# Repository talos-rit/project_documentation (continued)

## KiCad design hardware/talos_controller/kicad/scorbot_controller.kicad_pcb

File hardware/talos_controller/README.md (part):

# Talos controller board, rev 0.5

A controller board for the Scorbot ER-V and ER-4pc educational arms (the Talos-RIT project's two robots). It replaces the original
controller box with an ESP32-S3-DevKitC-1 on a 265 × 210 mm two-layer board: seven motor channels on plug-in driver
modules (five arm axes, the gripper, the slide rail; the project's own Talos driver module, or the Pololu G2 18v17 the sockets were drawn for), a hardware quadrature counter (LS7366R) and a current sense on every channel,
power from a standard ATX PC supply, a mushroom e-stop with a MOTORS ON relay chain, and ten status pixels. Every part is
through-hole, so the board can be built by hand or partly by a board house.

The firmware ([talos-rit/esp-driver](https://github.com/talos-rit/esp-driver)) speaks the Eshed controller's own serial dialect over the
DevKit's USB socket, so the Raspberry Pi "operator" software and the Pi image are the same for both robots. A protobuf link for the
ROS 2 stack is a second mode on the same socket, picked in the firmware's configuration or detected from the first bytes.

> **Status, 13 November 2026.** The design is rev 0.5: the reviewed rev 0.4 board with one change, two signals moved to other pins
> of the DevKit socket so that the ESP32 boards still on sale fit (section 8). The first order, from JLCPCB with partial
> assembly, is being prepared. No board has been built or powered yet, and the firmware compiles for the ESP32-S3 but has not run on a chip. Read
> everything here as "designed and reviewed, not yet proven"; the open items are listed at the end, and the first-power procedure
> in section 5 exists because the first board is the first test of the design.

Left to right, top to bottom: the seven channel strips (encoder filters, clamps and the LS7366R counters U13 to U19) across the top;
the rail terminal J8, the fan header J7 and its fuse F4 on the top edge; the DevKit socket U1 at the lower left with the I/O
expanders U9, U10 and the ADC boards U11, U12 beside it; the seven driver sockets U2 to U8 in the centre with the motor-rail
capacitors C42 to C45; the 50-pin robot connector J1 on the right edge; the relays K1, K2, the fuses F1, F2 and the ATX headers J2, J3 at
the lower right; the status pixels, the lamps, the MOTORS ON button SW2, the e-stop cut-out and the external e-stop terminal J4 along the
front edge.

## What is in this folder

| File | What it is |
| --- | --- |
| `README.md` | this guide |
| `parts.md` | the parts list by vendor, with quantities and the substitution rules |
| `fab/scorbot_controller_rev0.5_gerbers.zip` and `.sha256` | the manufacturing files (Gerbers and drill files): the zip to order from |
| `fab/jlcpcb_bom.csv`, `fab/jlcpcb_cpl.csv` | the BOM and placement files for JLCPCB's assembly service |
| `fab/hand_assembled.csv` | the parts JLCPCB does not place: what you fit yourself, and why |
| `fab/digikey_upload.csv` | the Digi-Key list, ready for "Upload a list" |
| `purchase_options.md`, `orders/` | three ways of ordering the boards, assembled or bare, with what each costs (carts of 18 November 2026) and the parts list of each cart |
| `schematic.pdf` | the schematic |
| `assembly_map.pdf`, `assembly_map.svg` | every footprint with its reference designator and orientation marks, and a legend of what goes where |
| `images/` | the board's top and bottom views |
| `kicad/` | the KiCad project: board, schematic, the project's symbol and footprint libraries. KiCad 7 format; KiCad 8, 9 and 10 open and upgrade it |

The design document behind the board, with the pin map, the channel design and the firmware's behaviour rules, is
`technical/ros2/esp_controller_design.md` in the project documentation (section 8 describes this board).

## What you need

- Through-hole soldering: about 36 parts to fit yourself (about 200 joints), plus the plug-in modules. A board house does the rest.
- A multimeter, a bench power supply with an adjustable current limit, and a clamp meter for the driver check.
- M3 hardware and standoffs of 15 mm or taller (the e-stop body reaches 12.6 mm below the board); the list is in `parts.md`.
- An ATX PC power supply with a 24-pin main lead and a 4-pin "CPU 12 V" lead.
- A computer with ESP-IDF v5.5.3 to build and flash the firmware, and two micro-USB **data** cables.
- A Raspberry Pi running the operator (the existing Talos-RIT stack), or a PC with the ROS 2 stack.

## 1. Order the board

Upload `fab/scorbot_controller_rev0.5_gerbers.zip` to JLCPCB as it is. Check the sha256 against `fab/scorbot_controller_rev0.5_gerbers.zip.sha256`
first if you copied it around. The options that matter:

| Option | Choose |
| --- | --- |
| Layers, size | 2 layers; 265 × 210 mm is read from the files (type it if the form still shows a default) |
| Material, thickness | FR-4 TG135, 1.6 mm |
| Copper | 1 oz outer copper (the design was checked at 1 oz; 2 oz is also fine with these files) |
| Surface finish | lead-free HASL. Not OSP: the hand-fitted parts are soldered weeks after the boards arrive |
| Colour | any; the white silkscreen on green is the most legible |
| Vias | tented, minimum via 0.3 mm (the design uses 0.4 mm drills) |
| Confirm production file | yes. Expect two remarks: the silkscreen text is 0.8 mm high, under JLCPCB's printed 1.0 mm minimum (accept it; it prints, a little less crisp), and three pads of U21 have an annular ring of exactly 0.20 mm, their minimum |
| Quantity | 5 is the minimum; spares are useful |

**Assembly.** Tick PCB assembly, top side, through-hole. Upload `fab/jlcpcb_bom.csv` as the BOM and `fab/jlcpcb_cpl.csv` as the
placement file. Choose "Economic" (it covers single-side through-hole boards of this size), tooling holes added by JLCPCB, **Confirm
parts placement = Yes** (you get a preview to check every polarised part: the diodes' bands, the electrolytics' stripes, the lamps,
the socket notches, the relays), board cleaning = No (the MOTORS ON switch is not washable), and add this assembly remark:

> All parts are through-hole, top side. Designators JH3-JH20 are 2.54 mm female header strips whose footprints have no pads on purpose:
> each strip is soldered into the holes of the module footprint under it (JH3-JH16 under U2-U8, JH17-JH20 under U11 and U12). Do NOT wash
> or clean the boards after soldering: SW2 (Omron B3F-4055) is not washable.

At the BOM step JLCPCB matches each line to its catalogue by the code in the file; one line, J4, has to be selected by hand (click its Search, enter `C480516`, Select), a quirk of their matcher with that part. A line it cannot match or has no stock for is simply left unticked: that
part moves to your own list (the fallback lines in `parts.md`). Two things to know: the BOM has the same resistor on two lines where it
is fitted flat and upright, which JLCPCB flags as a duplicate (tick both); and a few parts on the BOM are substitutes for the design
part that were accepted on their datasheets, which `fab/jlcpcb_bom.csv` names line by line.

## 2. Order the parts

What a whole order costs, with the boards assembled or bare, is in [`purchase_options.md`](purchase_options.md).

`parts.md` has everything by vendor: Digi-Key (upload `fab/digikey_upload.csv`, then delete the fallback lines you do not need),
the driver modules (five for the arm or seven for all channels: the Talos driver module in [`../talos_driver_module/`](../talos_driver_module/README.md),
designed and reviewed but not yet built or tested, or the Pololu G2 18v17 it replaces, which fits the same sockets), Adafruit and SparkFun (on the Digi-Key list), and
the supply, cables and hardware from anywhere. The rules that must not be broken when substituting are at the end of that file; the
three most important: the DevKit is never a variant ending in **V**, D20 and D25 are silicon rectifiers and never Schottkys, and F2 takes a
**1 A** blade fuse, never the 7.5 A of F1.

## 3. Assemble

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
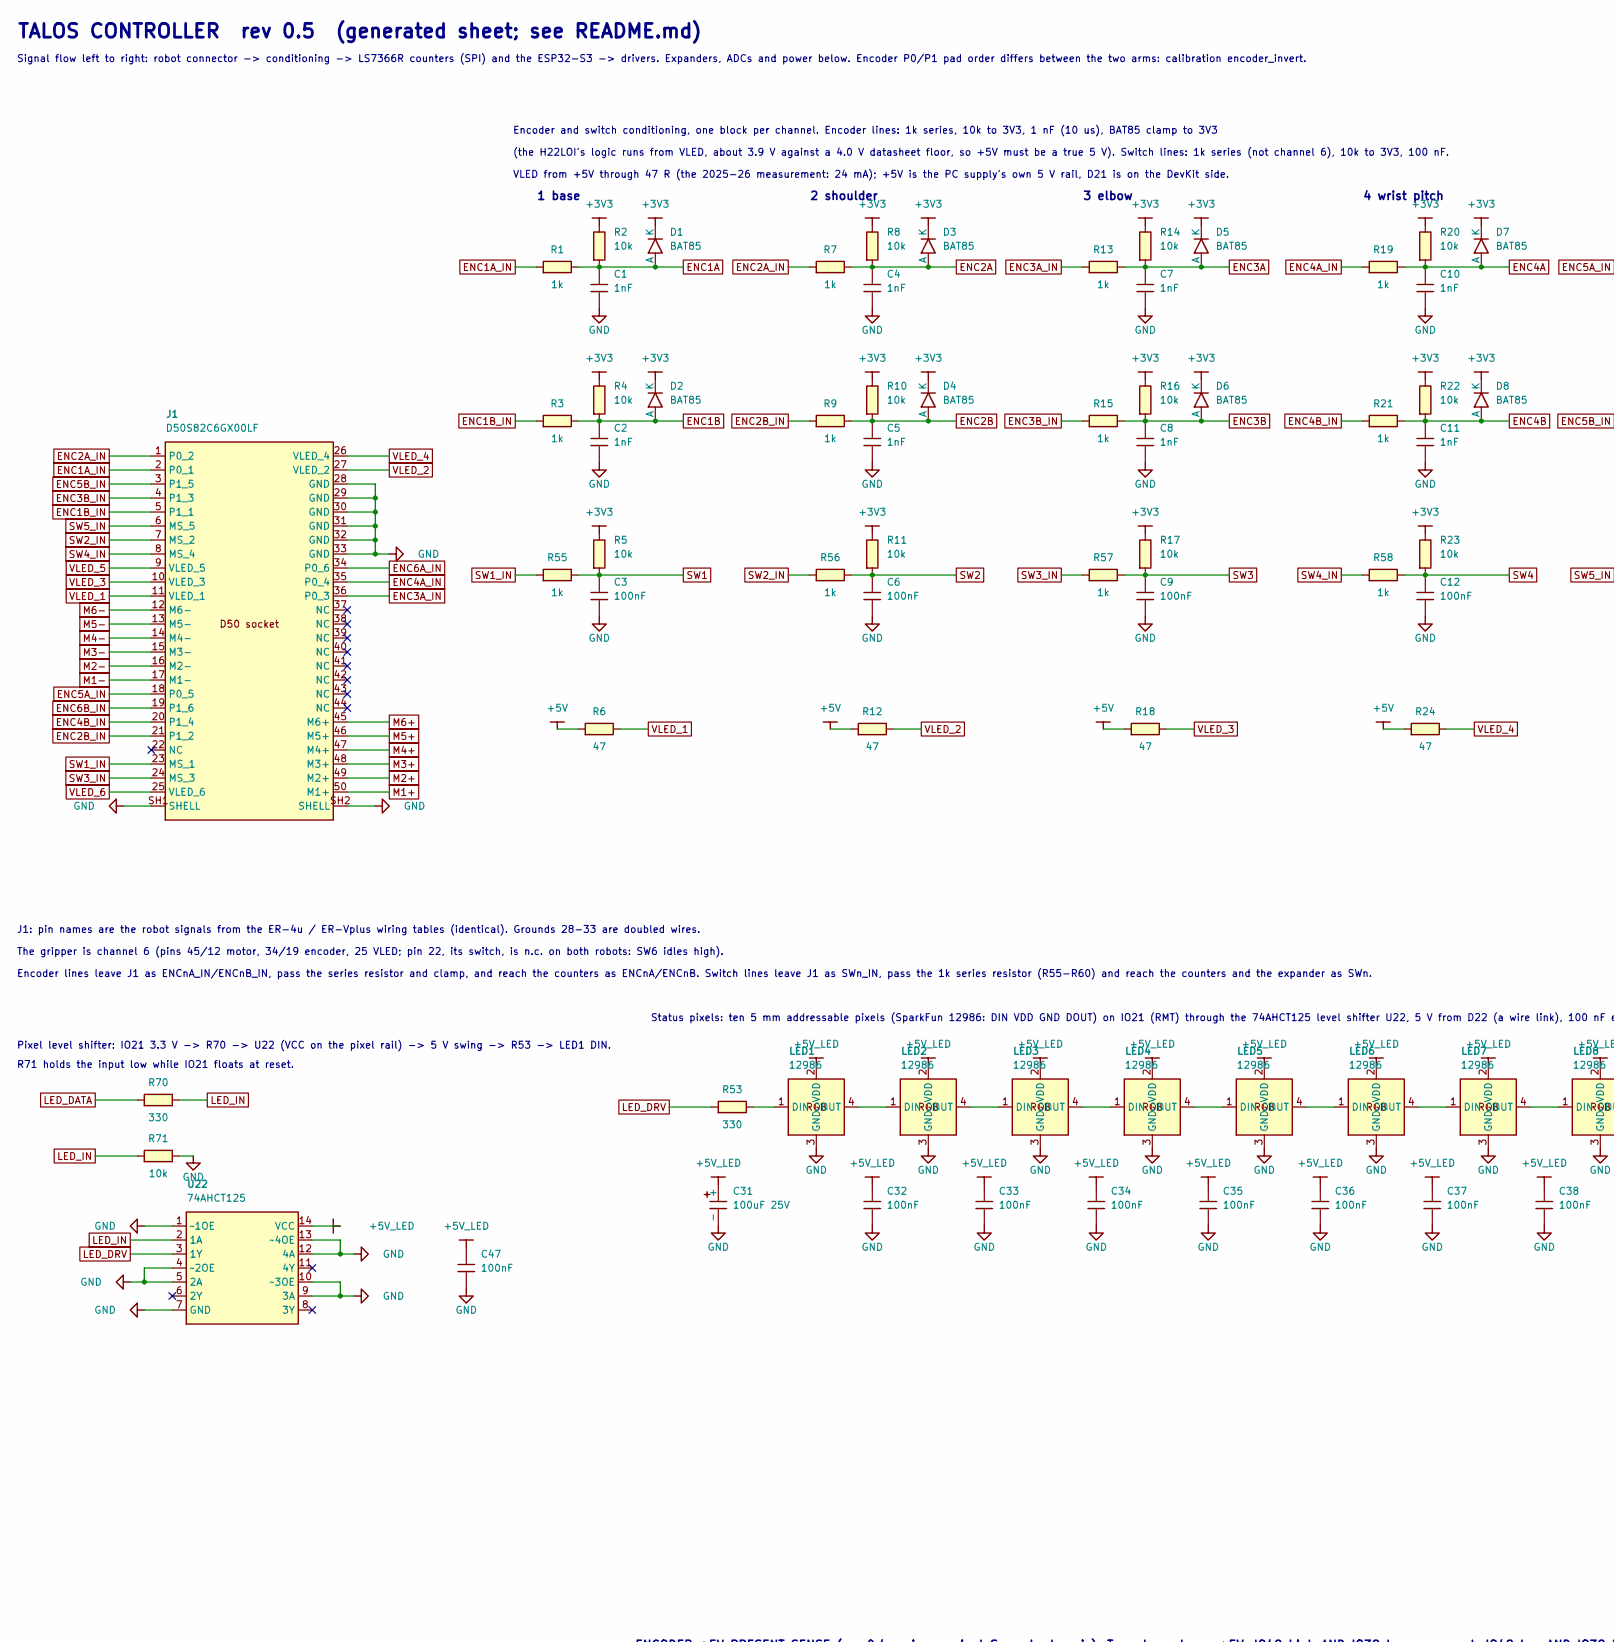
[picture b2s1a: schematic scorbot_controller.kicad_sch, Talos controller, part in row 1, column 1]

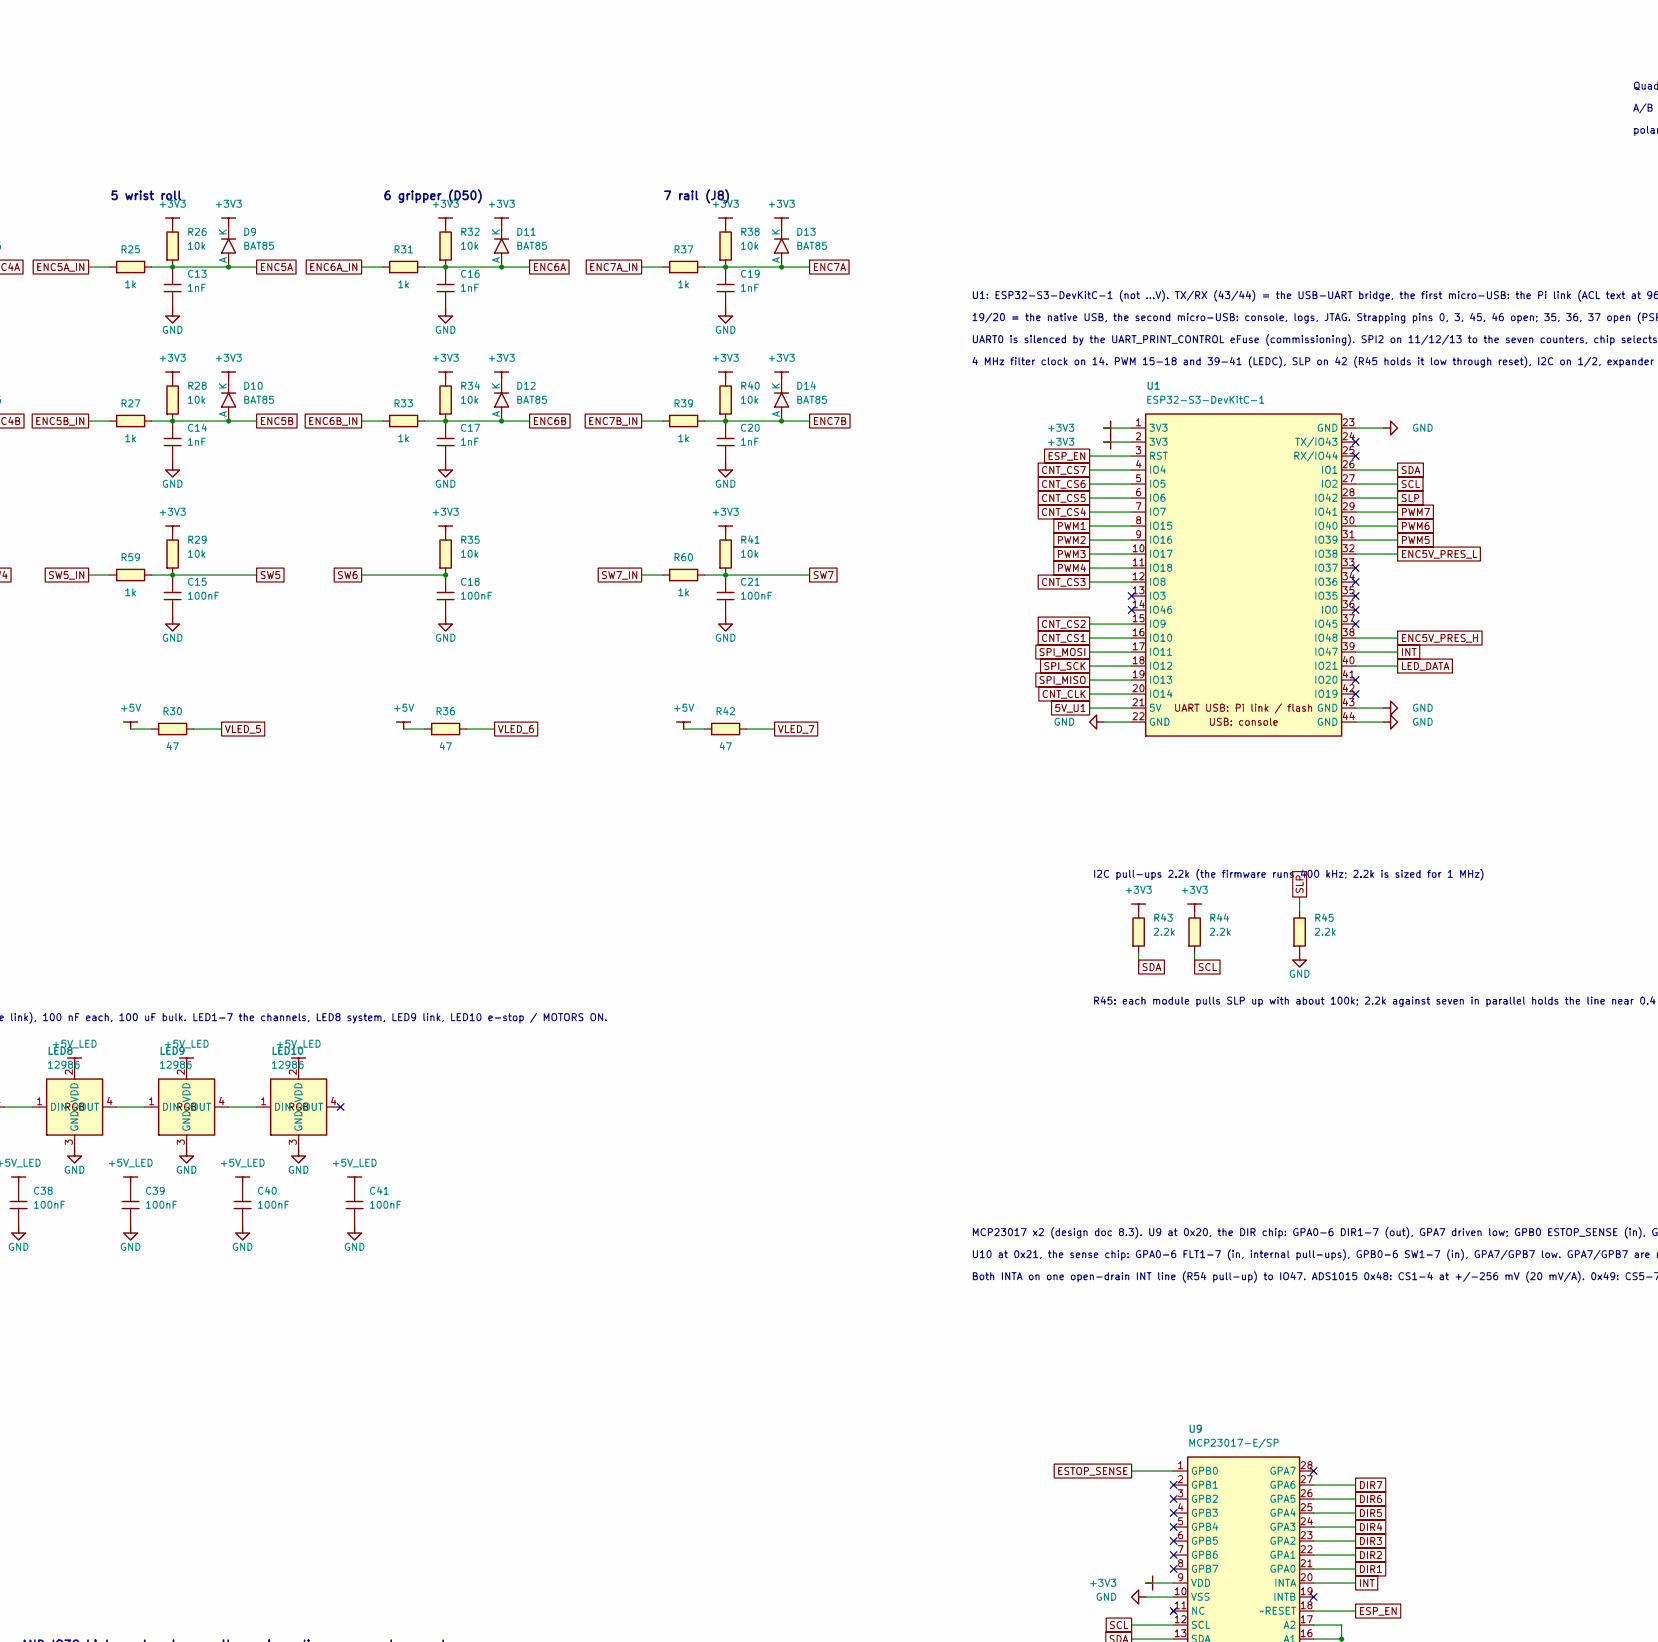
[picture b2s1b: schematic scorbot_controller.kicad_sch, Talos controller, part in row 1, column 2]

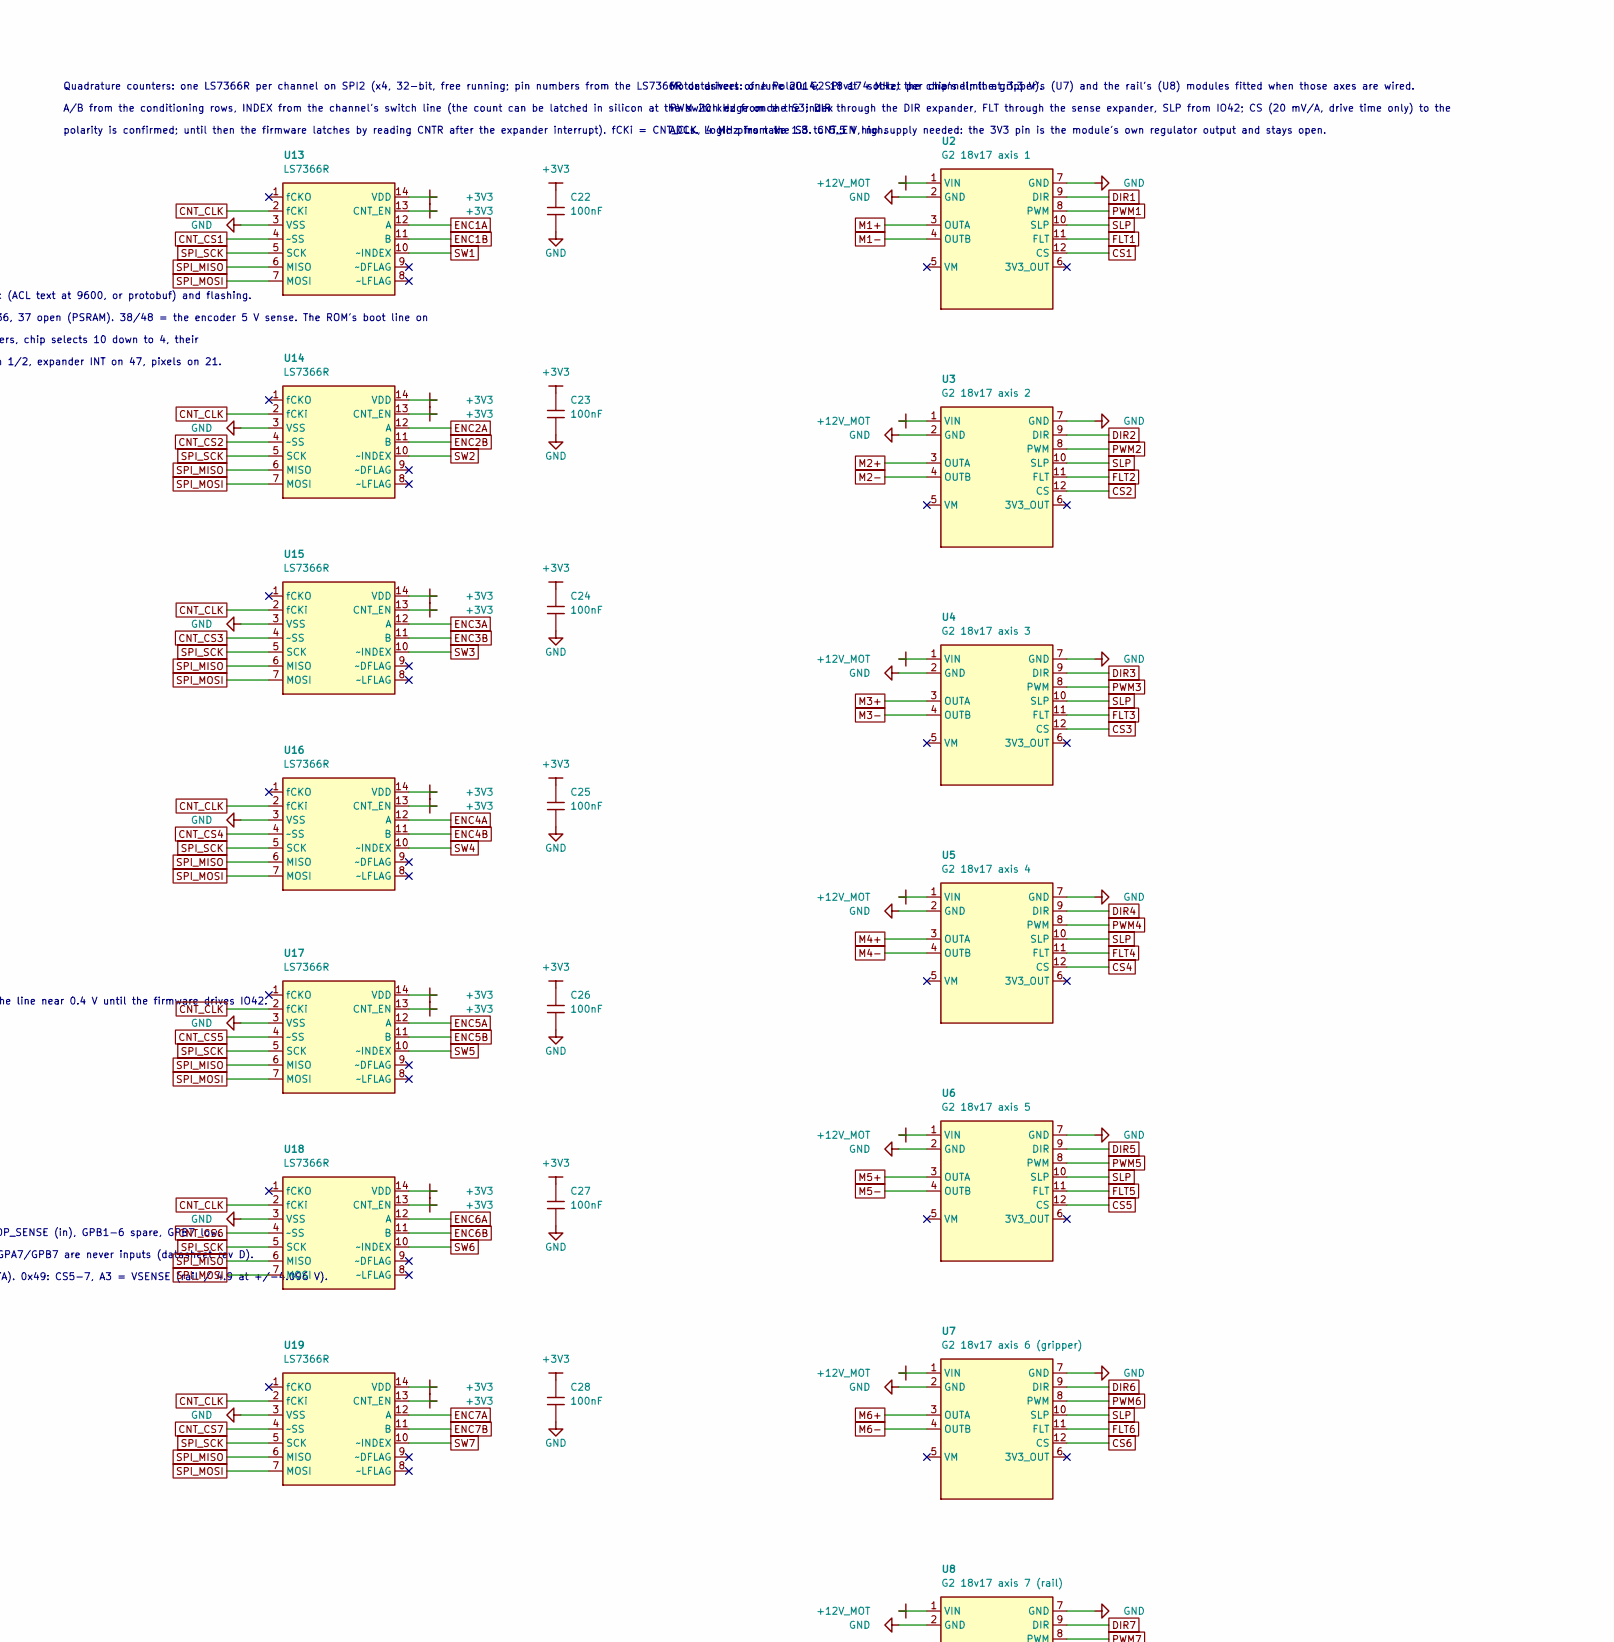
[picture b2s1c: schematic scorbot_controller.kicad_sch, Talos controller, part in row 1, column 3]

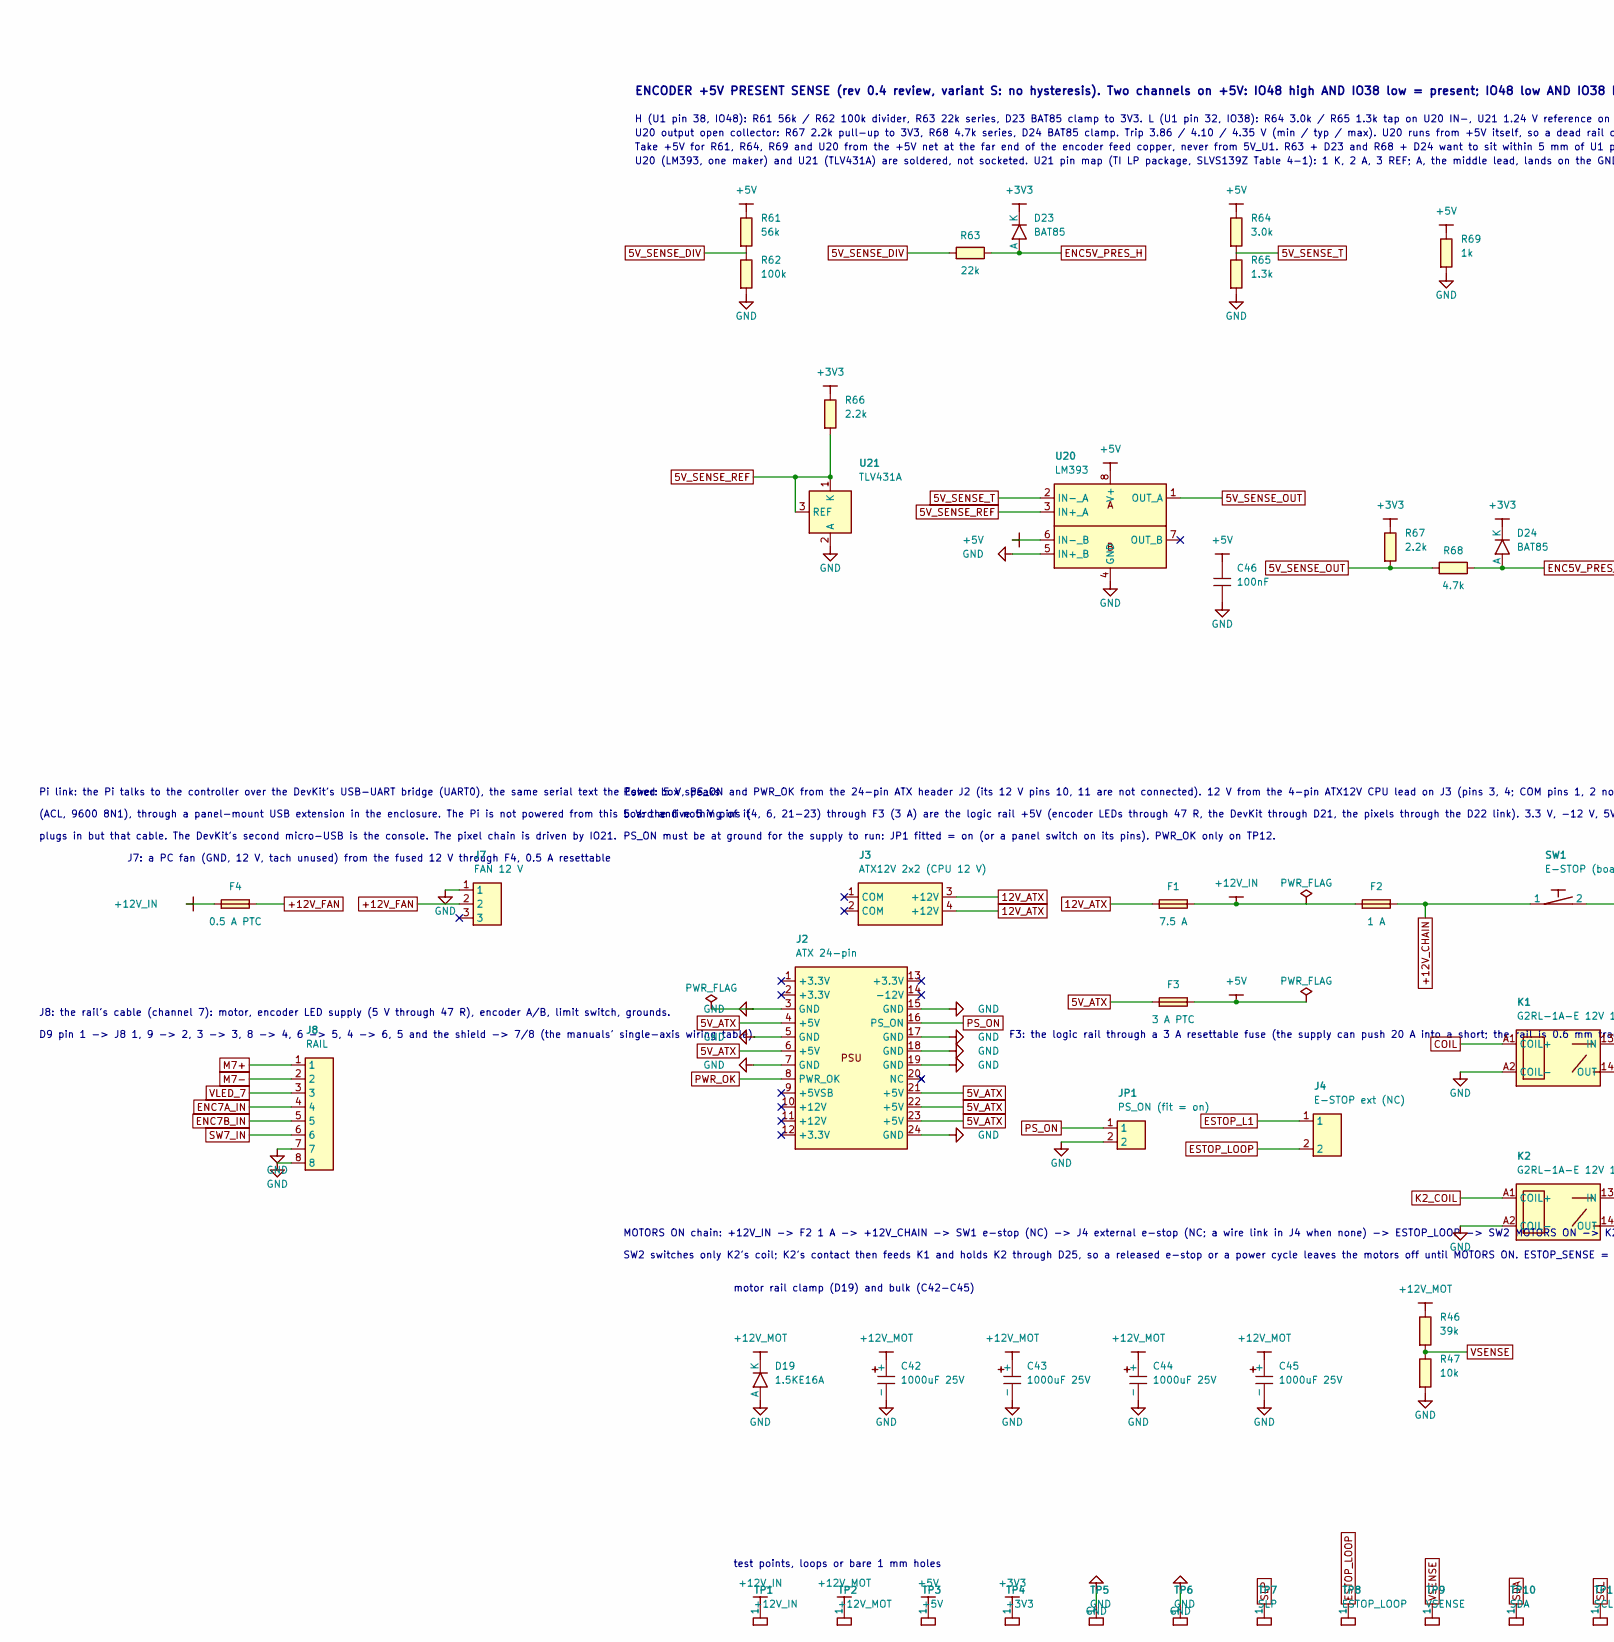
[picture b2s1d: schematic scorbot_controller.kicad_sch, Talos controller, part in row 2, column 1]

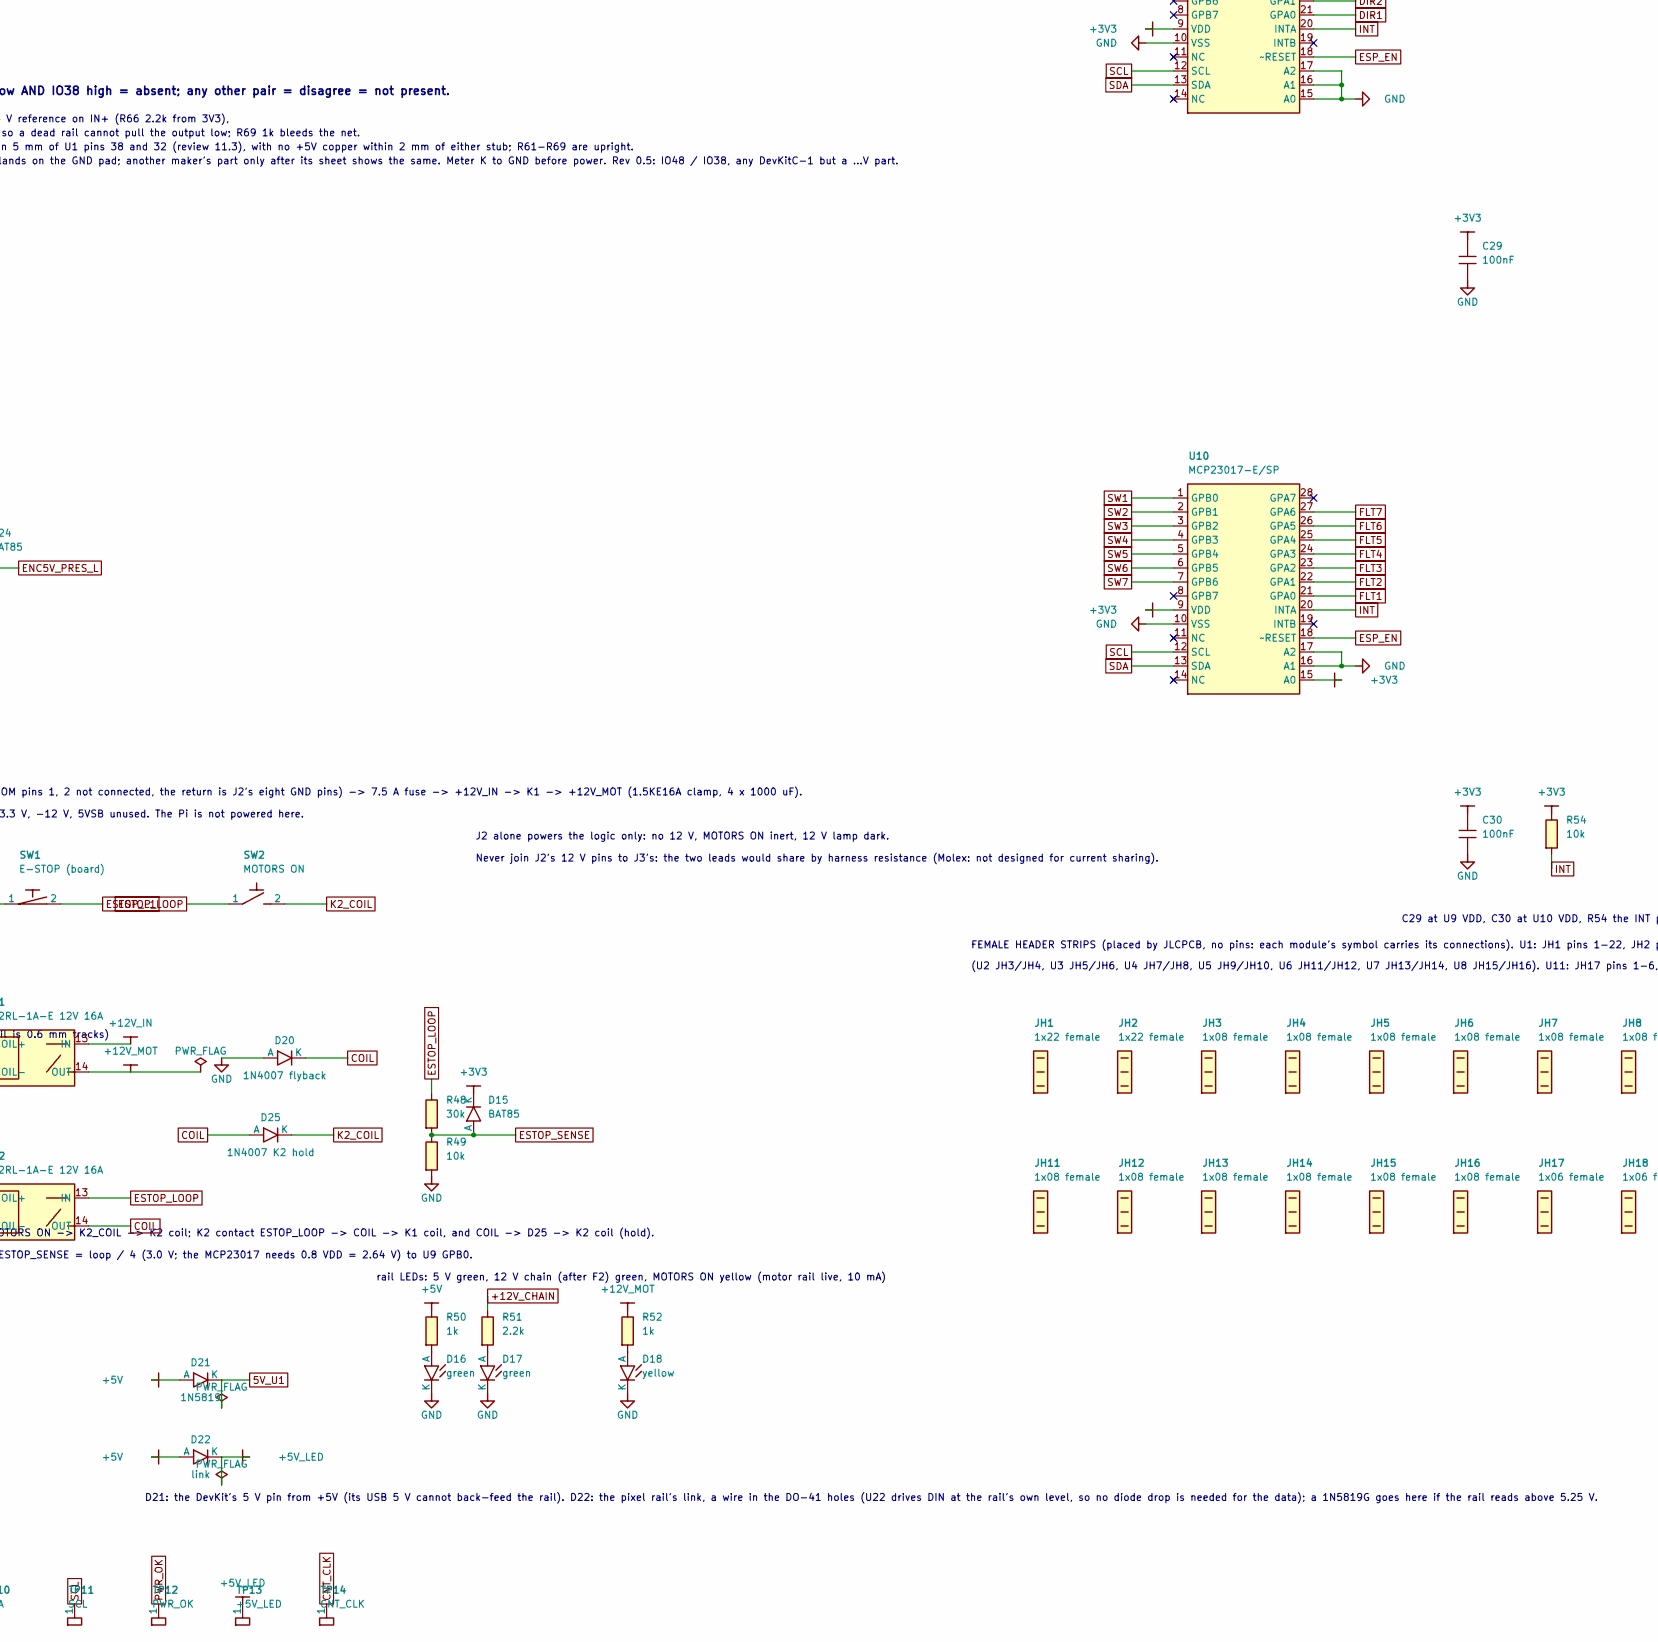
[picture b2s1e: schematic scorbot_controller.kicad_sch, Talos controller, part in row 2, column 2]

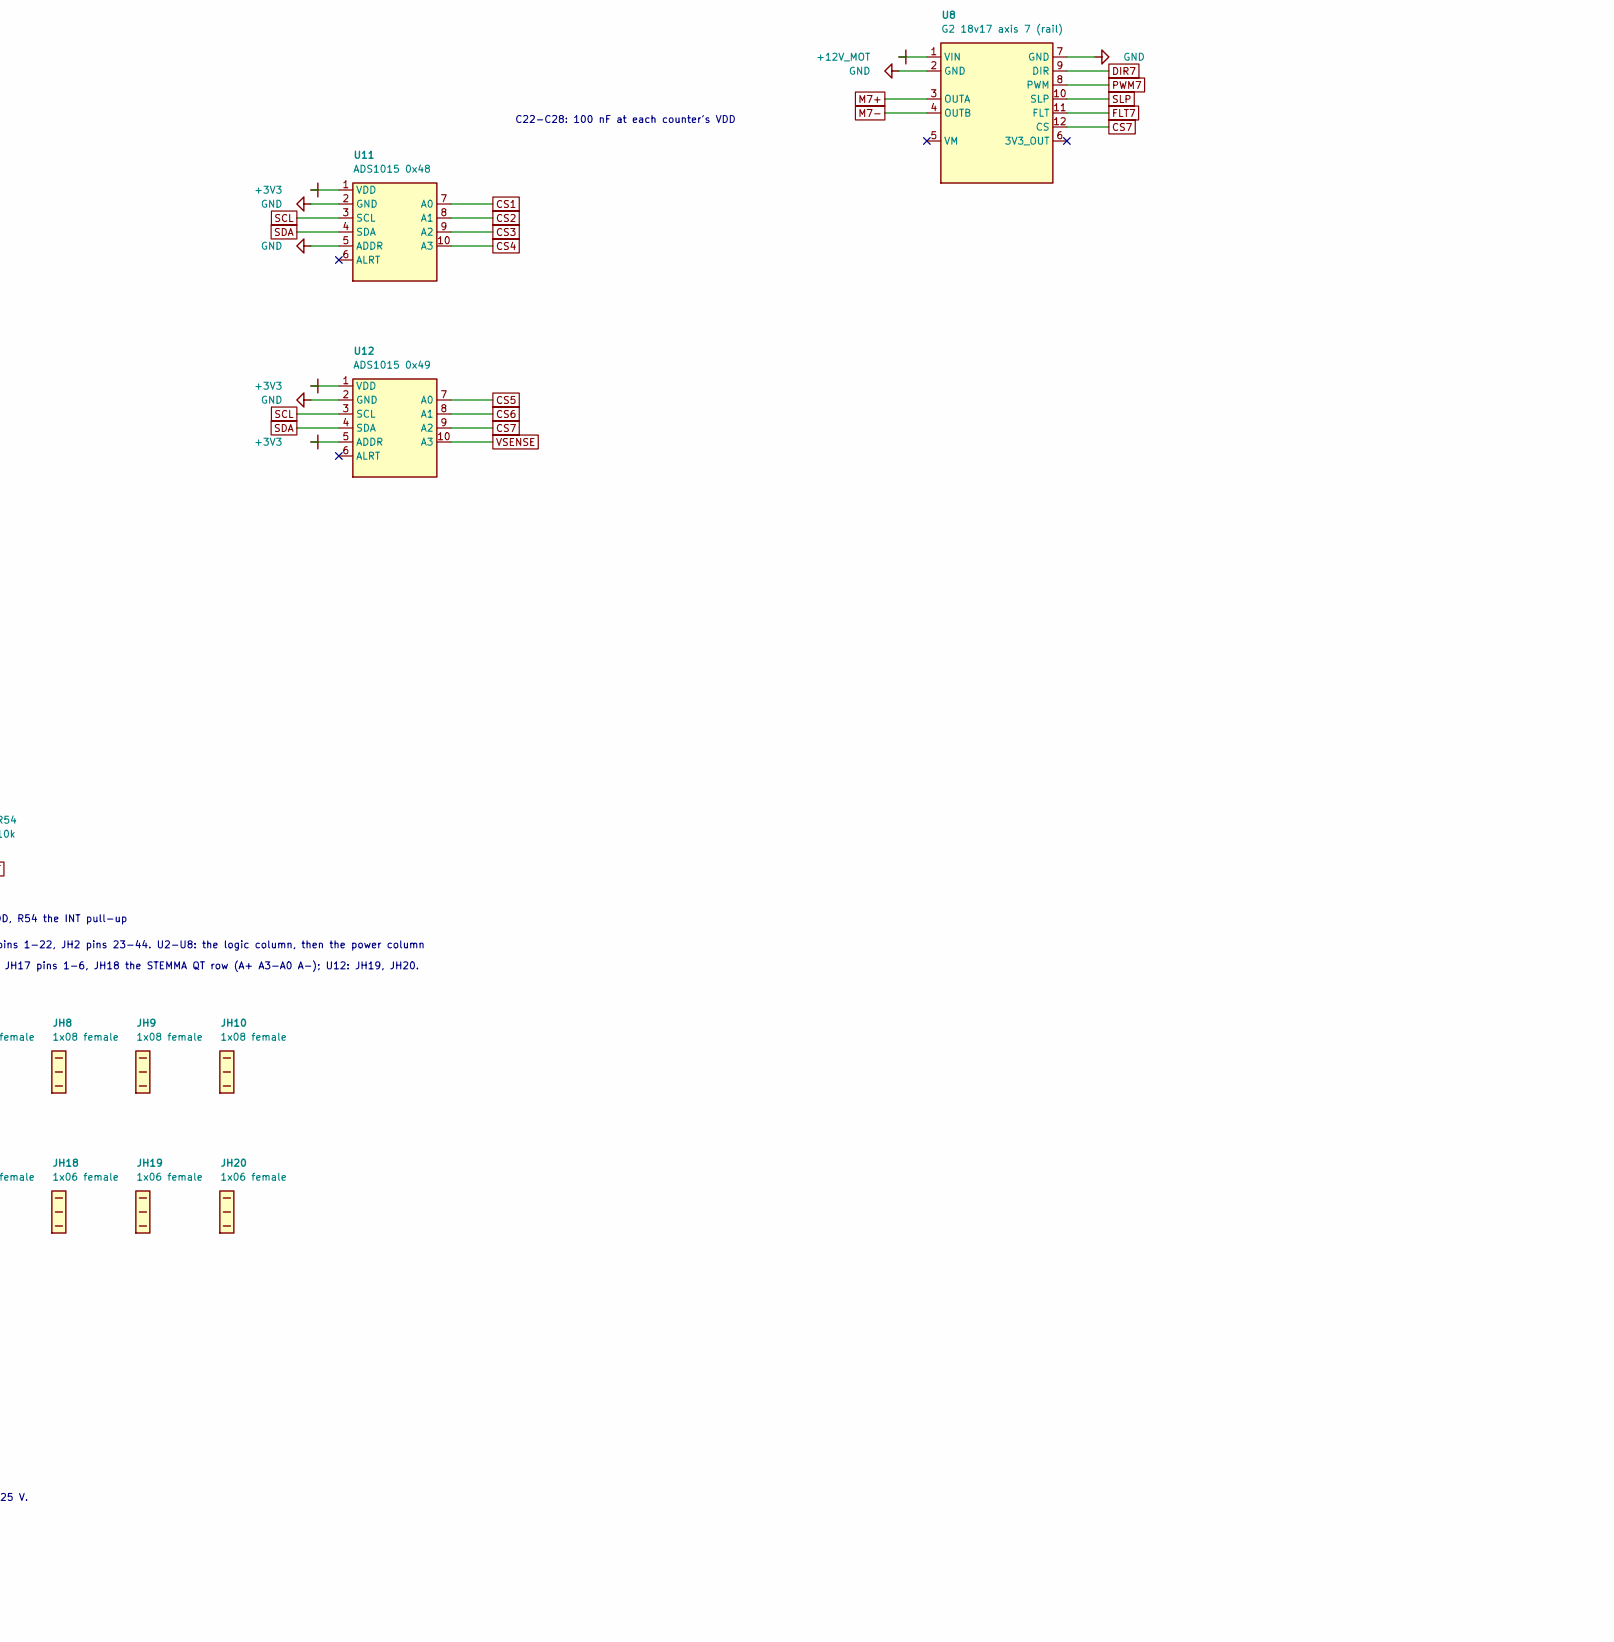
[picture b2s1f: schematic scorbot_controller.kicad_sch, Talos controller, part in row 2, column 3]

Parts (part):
C1, C2, C4, C5, C7, C8, C10, C11, C13, C14, C16, C17, C19, C20: 1nF; C_Disc_D5.0mm_W2.5mm_P5.00mm
C3, C6, C9, C12, C15, C18, C21, C22, C23, C24, C25, C26, C27, C28, C29, C30, C32, C33, C34, C35, C36, C37, C38, C39, C40, C41, C46, C47: 100nF; C_Disc_D5.0mm_W2.5mm_P5.00mm
C31: 100uF 25V; CP_Radial_D6.3mm_P2.50mm
C42, C43, C44, C45: 1000uF 25V; CP_Radial_D10.0mm_P5.00mm
D1, D2, D3, D4, D5, D6, D7, D8, D9, D10, D11, D12, D13, D14, D15, D23, D24: BAT85; D_DO-35_SOD27_P7.62mm_Horizontal
D16, D17: green; LED_D3.0mm
D18: yellow; LED_D3.0mm
D19: 1.5KE16A; D_DO-201AD_P15.24mm_Horizontal
D20: 1N4007 flyback; D_DO-41_SOD81_P10.16mm_Horizontal
D21: 1N5819; D_DO-41_SOD81_P10.16mm_Horizontal
D22: link; D_DO-41_SOD81_P10.16mm_Horizontal
D25: 1N4007 K2 hold; D_DO-41_SOD81_P10.16mm_Horizontal
F1: 7.5 A; FuseHolder_Blade_ATO_Littelfuse_FLR_178.6165
F2: 1 A; FuseHolder_Blade_ATO_Littelfuse_FLR_178.6165
F3: 3 A PTC; Fuse_Bourns_MF-RG400
F4: 0.5 A PTC; Fuse_Bourns_MF-RG400
J1: D50S82C6GX00LF; Amphenol_D50S82C6GX00LF
J2: ATX 24-pin; Molex_Mini-Fit_Jr_5569-24A2_2x12_P4.20mm_Horizontal
J3: ATX12V 2x2 (CPU 12 V); Molex_Mini-Fit_Jr_5569-04A2_2x02_P4.20mm_Horizontal
J4: E-STOP ext (NC); TerminalBlock_Phoenix_MKDS-1,5-2-5.08_1x02_P5.08mm_Horizont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
J7: FAN 12 V; PinHeader_1x03_P2.54mm_Vertical
J8: RAIL; TerminalBlock_Phoenix_MKDS-1,5-8-5.08_1x08_P5.08mm_Horizont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
JH1, JH2: 1x22 female; FemaleStrip_1x22_P2.54mm_NoCopper
JH3, JH4, JH5, JH6, JH7, JH8, JH9, JH10, JH11, JH12, JH13, JH14, JH15, JH16: 1x08 female; FemaleStrip_1x08_P2.54mm_NoCopper
JH17, JH18, JH19, JH20: 1x06 female; FemaleStrip_1x06_P2.54mm_NoCopper
JP1: PS_ON (fit = on); PinHeader_1x02_P2.54mm_Vertical
K1, K2: G2RL-1A-E 12V 16A; Relay_SPST_Omron_G2RL-1A-E
LED1, LED2, LED3, LED4, LED5, LED6, LED7, LED8, LED9, LED10: 12986; Pixel_5mm_DIN_VDD_GND_DOUT_Staggered
R1, R3, R7, R9, R13, R15, R19, R21, R25, R27, R31, R33, R37, R39, R50, R52: 1k; R_Axial_DIN0207_L6.3mm_D2.5mm_P10.16mm_Horizontal
R2, R4, R5, R8, R10, R11, R14, R16, R17, R20, R22, R23, R26, R28, R29, R32, R34, R35, R38, R40, R41, R47, R49, R54: 10k; R_Axial_DIN0207_L6.3mm_D2.5mm_P10.16mm_Horizontal
R6, R12, R18, R24, R30, R36, R42: 47; R_Axial_DIN0207_L6.3mm_D2.5mm_P10.16mm_Horizontal
R43, R44, R45, R51: 2.2k; R_Axial_DIN0207_L6.3mm_D2.5mm_P10.16mm_Horizontal
R46: 39k; R_Axial_DIN0207_L6.3mm_D2.5mm_P10.16mm_Horizontal
R48: 30k; R_Axial_DIN0207_L6.3mm_D2.5mm_P10.16mm_Horizontal
R53: 330; R_Axial_DIN0207_L6.3mm_D2.5mm_P10.16mm_Horizontal
R55, R56, R57, R58, R59, R60, R69: 1k; R_Axial_DIN0207_L6.3mm_D2.5mm_P2.54mm_Vertical
R61: 56k; R_Axial_DIN0207_L6.3mm_D2.5mm_P2.54mm_Vertical
R62: 100k; R_Axial_DIN0207_L6.3mm_D2.5mm_P2.54mm_Vertical
R63: 22k; R_Axial_DIN0207_L6.3mm_D2.5mm_P2.54mm_Vertical
R64: 3.0k; R_Axial_DIN0207_L6.3mm_D2.5mm_P2.54mm_Vertical
R65: 1.3k; R_Axial_DIN0207_L6.3mm_D2.5mm_P2.54mm_Vertical
R66, R67: 2.2k; R_Axial_DIN0207_L6.3mm_D2.5mm_P2.54mm_Vertical
R68: 4.7k; R_Axial_DIN0207_L6.3mm_D2.5mm_P2.54mm_Vertical
R70: 330; R_Axial_DIN0207_L6.3mm_D2.5mm_P2.54mm_Vertical
R71: 10k; R_Axial_DIN0207_L6.3mm_D2.5mm_P2.54mm_Vertical
SW1: E-STOP (board); Estop_16mm_IDEC_XA1E
SW2: MOTORS ON; SW_PUSH-12mm_B3F
TP1: +12V_IN; TestPoint_Loop_D2.50mm_Drill1.0mm
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
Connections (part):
5V_ATX: F3.1, J2.4 (+5V), J2.6 (+5V), J2.21 (+5V), J2.22 (+5V), J2.23 (+5V)
5V_SENSE_DIV: R61.2, R62.1, R63.1
5V_SENSE_OUT: R67.2, R68.1, U20.1 (OUT_A)
5V_SENSE_REF: R66.2, U20.3 (IN+_A), U21.1 (K), U21.3 (REF)
5V_SENSE_T: R64.2, R65.1, U20.2 (IN-_A)
5V_U1: D21.1 (K), U1.21 (5V)
12V_ATX: F1.1, J3.3 (+12V), J3.4 (+12V)
+3V3: C22.1, C23.1, C24.1, C25.1, C26.1, C27.1, C28.1, C29.1, C30.1, D1.1 (K), D2.1 (K), D3.1 (K), D4.1 (K), D5.1 (K), D6.1 (K), D7.1 (K), D8.1 (K), D9.1 (K), D10.1 (K), D11.1 (K), D12.1 (K), D13.1 (K), D14.1 (K), D15.1 (K), D23.1 (K), D24.1 (K), R2.1, R4.1, R5.1, R8.1, R10.1, R11.1, R14.1, R16.1, R17.1, R20.1, R22.1, R23.1, R26.1, R28.1, R29.1, R32.1, R34.1, R35.1, R38.1, R40.1, R41.1, R43.1, R44.1, R54.1, R66.1, R67.1, TP4.1, U1.1 (3V3), U1.2 (3V3), U9.9 (VDD), U10.9 (VDD), U10.15 (A0), U11.1 (VDD), U12.1 (VDD), U12.5 (ADDR), U13.13 (CNT_EN), U13.14 (VDD), U14.13 (CNT_EN), U14.14 (VDD), U15.13 (CNT_EN), U15.14 (VDD), U16.13 (CNT_EN), U16.14 (VDD), U17.13 (CNT_EN), U17.14 (VDD), U18.13 (CNT_EN), U18.14 (VDD), U19.13 (CNT_EN), U19.14 (VDD)
+5V: C46.1, D21.2 (A), D22.2 (A), F3.2, R6.1, R12.1, R18.1, R24.1, R30.1, R36.1, R42.1, R50.1, R61.1, R64.1, R69.1, TP3.1, U20.6 (IN-_B), U20.8 (V+)
+5V_LED: C31.1 (+), C32.1, C33.1, C34.1, C35.1, C36.1, C37.1, C38.1, C39.1, C40.1, C41.1, C47.1, D22.1 (K), LED1.2 (VDD), LED2.2 (VDD), LED3.2 (VDD), LED4.2 (VDD), LED5.2 (VDD), LED6.2 (VDD), LED7.2 (VDD), LED8.2 (VDD), LED9.2 (VDD), LED10.2 (VDD), TP13.1, U22.14 (VCC)
+12V_CHAIN: F2.2, R51.1, SW1.1
+12V_FAN: F4.2, J7.2
+12V_IN: F1.2, F2.1, F4.1, K1.13 (IN), TP1.1
+12V_MOT: C42.1 (+), C43.1 (+), C44.1 (+), C45.1 (+), D19.1 (K), K1.14 (OUT), R46.1, R52.1, TP2.1, U2.1 (VIN), U3.1 (VIN), U4.1 (VIN), U5.1 (VIN), U6.1 (VIN), U7.1 (VIN), U8.1 (VIN)
CNT_CLK: TP14.1, U1.20 (IO14), U13.2 (fCKi), U14.2 (fCKi), U15.2 (fCKi), U16.2 (fCKi), U17.2 (fCKi), U18.2 (fCKi), U19.2 (fCKi)
CNT_CS1: U1.16 (IO10), U13.4 (~SS)
CNT_CS2: U1.15 (IO9), U14.4 (~SS)
CNT_CS3: U1.12 (IO8), U15.4 (~SS)
CNT_CS4: U1.7 (IO7), U16.4 (~SS)
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
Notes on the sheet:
TALOS CONTROLLER rev 0.5 (generated sheet; see README.md)
Signal flow left to right: robot connector -> conditioning -> LS7366R counters (SPI) and the ESP32-S3 -> drivers. Expanders, ADCs and power below. Encoder P0/P1 pad order differs between the two arms: calibration encoder_invert.
J1: pin names are the robot signals from the ER-4u / ER-Vplus wiring tables (identical). Grounds 28-33 are doubled wires.
The gripper is channel 6 (pins 45/12 motor, 34/19 encoder, 25 VLED; pin 22, its switch, is n.c. on both robots: SW6 idles high).
Encoder lines leave J1 as ENCnA_IN/ENCnB_IN, pass the series resistor and clamp, and reach the counters as ENCnA/ENCnB. Switch lines leave J1 as SWn_IN, pass the 1k series resistor (R55-R60) and reach the counters and the expander as SWn.
Encoder and switch conditioning, one block per channel. Encoder lines: 1k series, 10k to 3V3, 1 nF (10 us), BAT85 clamp to 3V3
(the H22LOI's logic runs from VLED, about 3.9 V against a 4.0 V datasheet floor, so +5V must be a true 5 V). Switch lines: 1k series (not channel 6), 10k to 3V3, 100 nF.
VLED from +5V through 47 R (the 2025-26 measurement: 24 mA); +5V is the PC supply's own 5 V rail, D21 is on the DevKit side.
1 base
2 shoulder
3 elbow
4 wrist pitch
5 wrist roll
6 gripper (D50)
7 rail (J8)
U1: ESP32-S3-DevKitC-1 (not ...V). TX/RX (43/44) = the USB-UART bridge, the first micro-USB: the Pi link (ACL text at 9600, or protobuf) and flashing.
19/20 = the native USB, the second micro-USB: console, logs, JTAG. Strapping pins 0, 3, 45, 46 open; 35, 36, 37 open (PSRAM). 38/48 = the encoder 5 V sense. The ROM's boot line on
UART0 is silenced by the UART_PRINT_CONTROL eFuse (commissioning). SPI2 on 11/12/13 to the seven counters, chip selects 10 down to 4, their
4 MHz filter clock on 14. PWM 15-18 and 39-41 (LEDC), SLP on 42 (R45 holds it low through reset), I2C on 1/2, expander INT on 47, pixels on 21.
I2C pull-ups 2.2k (the firmware runs 400 kHz; 2.2k is sized for 1 MHz)
R45: each module pulls SLP up with about 100k; 2.2k against seven in parallel holds the line near 0.4 V until the firmware drives IO42.
Quadrature counters: one LS7366R per channel on SPI2 (x4, 32-bit, free running; pin numbers from the LS7366R datasheet of June 2014; SPI at 4 MHz, the chip's limit at 3.3 V).
A/B from the conditioning rows, INDEX from the channel's switch line (the count can be latched in silicon at the switch edge once the index
polarity is confirmed; until then the firmware latches by reading CNTR after the expander interrupt). fCKi = CNT_CLK, 4 MHz from the S3. CNT_EN high.
C22-C28: 100 nF at each counter's VDD
Motor drivers: one Pololu G2 18v17 socket per channel; the gripper's (U7) and the rail's (U8) modules fitted when those axes are wired.
PWM 20 kHz from the S3; DIR through the DIR expander, FLT through the sense expander, SLP from IO42; CS (20 mV/A, drive time only) to the
ADCs. Logic pins take 1.8 to 5.5 V, no supply needed: the 3V3 pin is the module's own regulator output and stays open.
MCP23017 x2 (design doc 8.3). U9 at 0x20, the DIR chip: GPA0-6 DIR1-7 (out), GPA7 driven low; GPB0 ESTOP_SENSE (in), GPB1-6 spare, GPB7 low.
U10 at 0x21, the sense chip: GPA0-6 FLT1-7 (in, internal pull-ups), GPB0-6 SW1-7 (in), GPA7/GPB7 low. GPA7/GPB7 are never inputs (datasheet rev D).
Both INTA on one open-drain INT line (R54 pull-up) to IO47. ADS1015 0x48: CS1-4 at +/-256 mV (20 mV/A). 0x49: CS5-7, A3 = VSENSE (rail / 4.9 at +/-4.096 V).
C29 at U9 VDD, C30 at U10 VDD, R54 the INT pull-up
Power: 5 V, PS_ON and PWR_OK from the 24-pin ATX header J2 (its 12 V pins 10, 11 are not connected). 12 V from the 4-pin ATX12V CPU lead on J3 (pins 3, 4; COM pins 1, 2 not connected, the return is J2's eight GND pins) -> 7.5 A fuse -> +12V_IN -> K1 -> +12V_MOT (1.5KE16A clamp, 4 x 1000 uF).
5 V: the five 5 V pins (4, 6, 21-23) through F3 (3 A) are the logic rail +5V (encoder LEDs through 47 R, the DevKit through D21, the pixels through the D22 link). 3.3 V, -12 V, 5VSB unused. The Pi is not powered here.
PS_ON must be at ground for the supply to run: JP1 fitted = on (or a panel switch on its pins). PWR_OK only on TP12.
F3: the logic rail through a 3 A resettable fuse (the supply can push 20 A into a short; the rail is 0.6 mm tracks)
J2 alone powers the logic only: no 12 V, MOTORS ON inert, 12 V lamp dark.
Never join J2's 12 V pins to J3's: the two leads would share by harness resistance (Molex: not designed for current sharing).
MOTORS ON chain: +12V_IN -> F2 1 A -> +12V_CHAIN -> SW1 e-stop (NC) -> J4 external e-stop (NC; a wire link in J4 when none) -> ESTOP_LOOP -> SW2 MOTORS ON -> K2_COIL -> K2 coil; K2 contact ESTOP_LOOP -> COIL -> K1 coil, and COIL -> D25 -> K2 coil (hold).
SW2 switches only K2's coil; K2's contact then feeds K1 and holds K2 through D25, so a released e-stop or a power cycle leaves the motors off until MOTORS ON. ESTOP_SENSE = loop / 4 (3.0 V; the MCP23017 needs 0.8 VDD = 2.64 V) to U9 GPB0.
